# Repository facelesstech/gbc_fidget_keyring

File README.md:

# gbc_fidget_keyring
gbc_fidget_keyring
* [Blog post](https://facelesstech.wordpress.com/2023/10/22/gameboy-color-fidget-keyring/)

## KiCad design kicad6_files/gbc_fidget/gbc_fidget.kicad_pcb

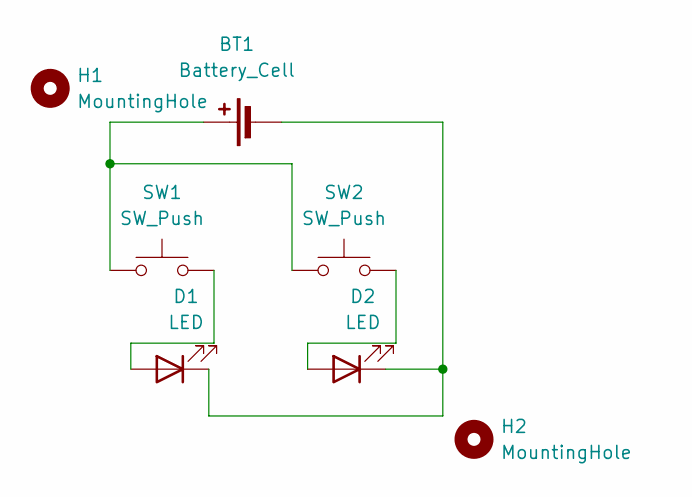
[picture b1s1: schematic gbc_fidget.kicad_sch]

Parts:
BT1: Battery_Cell; BatteryHolder_Keystone_3034_1x20mm
D1, D2: LED; LED_0603_1608Metric_Pad1.05x0.95mm_HandSolder
H1, H2: MountingHole; MountingHole_2.1mm
SW1, SW2: SW_Push; gbc_pad_buttons_small

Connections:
unnamed: BT1.1 (+), SW1.1, SW2.1
unnamed: BT1.2 (-), D1.1 (K), D2.1 (K)
unnamed: D1.2 (A), SW1.2
unnamed: D2.2 (A), SW2.2

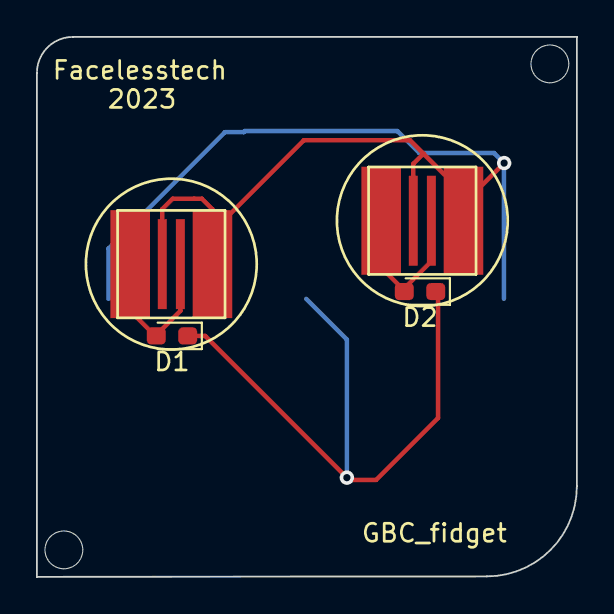
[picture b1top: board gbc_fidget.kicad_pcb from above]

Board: 2 copper layers, 30.0 x 30.0 mm, 7 parts (1 on the bottom side), 4 nets.

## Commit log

2023-10-14 added license
2023-10-14 added 3d print files, stl and freecad
2023-10-14 added kicad PCB files
2023-10-15 added photo
2023-10-15 added photo to readme
2023-10-15 fixed blog post link even tho its the wrong link
2023-10-15 fixed blog post link
2023-10-15 fixed blog post link again
2023-10-22 fixed blog post link again1
